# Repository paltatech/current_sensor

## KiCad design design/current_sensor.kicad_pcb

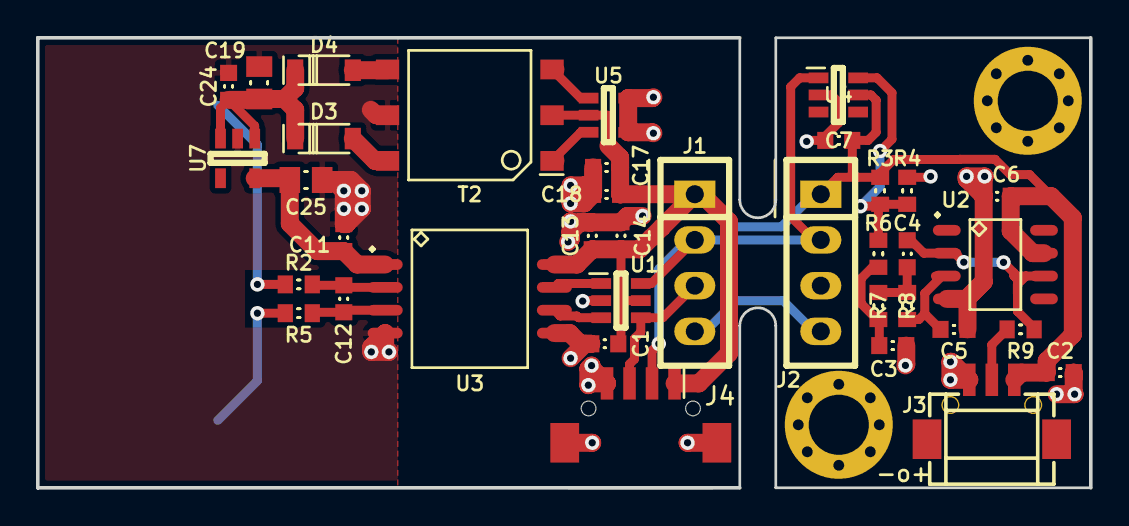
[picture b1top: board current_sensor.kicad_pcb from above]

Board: 2 copper layers, 58.5 x 25.0 mm, 40 parts (1 on the bottom side), 22 nets.

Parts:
C1, C6, C7, C11, C13, C18, C24: 100nF; CAPC1608X55
C2: 10uF; CAPC1608X55
C3: 470pF; CAPC1608X55
C4, C12: 330pF; CAPC1608X55
C5: 150pF; CAPC1608X55
C14, C17: 2.2uF; CAPC1608X55
C19, C25: 22uF; CAPC2012X70
D3, D4: MBR0520; SOD-123
HOLE1, HOLE2: MOUNTING_HOLE; PTH-3MM-PLUS-SUPPORTED
J1, J2: DS conn; CONN-100MIL-F-1x4
J3: Conn; DF13-3P-1.25H_50
J4: DS conn; DF13-4P-1.25H(50)
R1: 0.035uOhm; BAS-M-R0002
R2, R5: 1k; RESC1608X50
R3, R4: 100k; RESC1608X50
R6: 910R; RESC1608X50
R7: 6.8k; RESC1608X50
R8: 5.1k; RESC1608X50
R9: 220R; RESC1608X50
T2: TRANS-2CT; WURTH-760390014
U1, U4: Buffer; SOT-23-6
U2: OPA376AID; SOIC127P600X175-8
U3: AMC1303; SOIC127P1032X265-8
U5: SN6501DBV; SOT-23-5
U7: TPS76350; SOT-23-5

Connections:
+5: C1.1, C2.1, C6.1, C7.1, C13.1, C14.1, C17.1, C18.1, J1.1, J2.1, J3.1, J4.1, R3.1, T2.2, U1.5, U2.7, U3.8, U4.5, U5.2
/analog filter/OUT: J3.2, R9.1
/clk: J1.3, J4.3, U1.4
/current sensor/CLK: U1.3, U3.6
/current sensor/DATA: U1.1, U3.7
/current sensor/VDD2: C11.1, C25.1, U3.1, U7.5
/current sensor/VIN-: C12.2, R5.2, U3.3
/current sensor/Vin+: R1.1, R2.1
/delta_sigma: J1.2, J2.2, J4.2, U1.6, U4.1
GND: C1.2, C2.2, C3.2, C5.2, C6.2, C7.2, C13.2, C14.2, C17.2, C18.2, J1.4, J2.4, J3.3, J4.4, R4.2, U1.2, U2.4, U3.5, U4.2, U5.4, U5.5
ISOGND: C11.2, C19.2, C24.2, C25.2, R1.2, R5.1, T2.5, U3.4, U7.2
unnamed: C3.1, R6.1, R7.2
unnamed: C4.1, R9.2, U2.2, U2.6
unnamed: C4.2, R7.1, R8.2
unnamed: C5.1, R8.1, U2.3
unnamed: C12.1, R2.2, U3.2
unnamed: C19.1, C24.1, D3.1, D4.1, U7.1, U7.3
unnamed: D3.2, T2.6
unnamed: D4.2, T2.4
unnamed: R3.2, R4.1, R6.2, U4.6
unnamed: T2.1, U5.3
unnamed: T2.3, U5.1

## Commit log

2017-08-15 Updated BOM and added libraries
2017-08-18 Added buffer to restore signal before opamp analog filter
2017-08-30 Added harness fault protections
